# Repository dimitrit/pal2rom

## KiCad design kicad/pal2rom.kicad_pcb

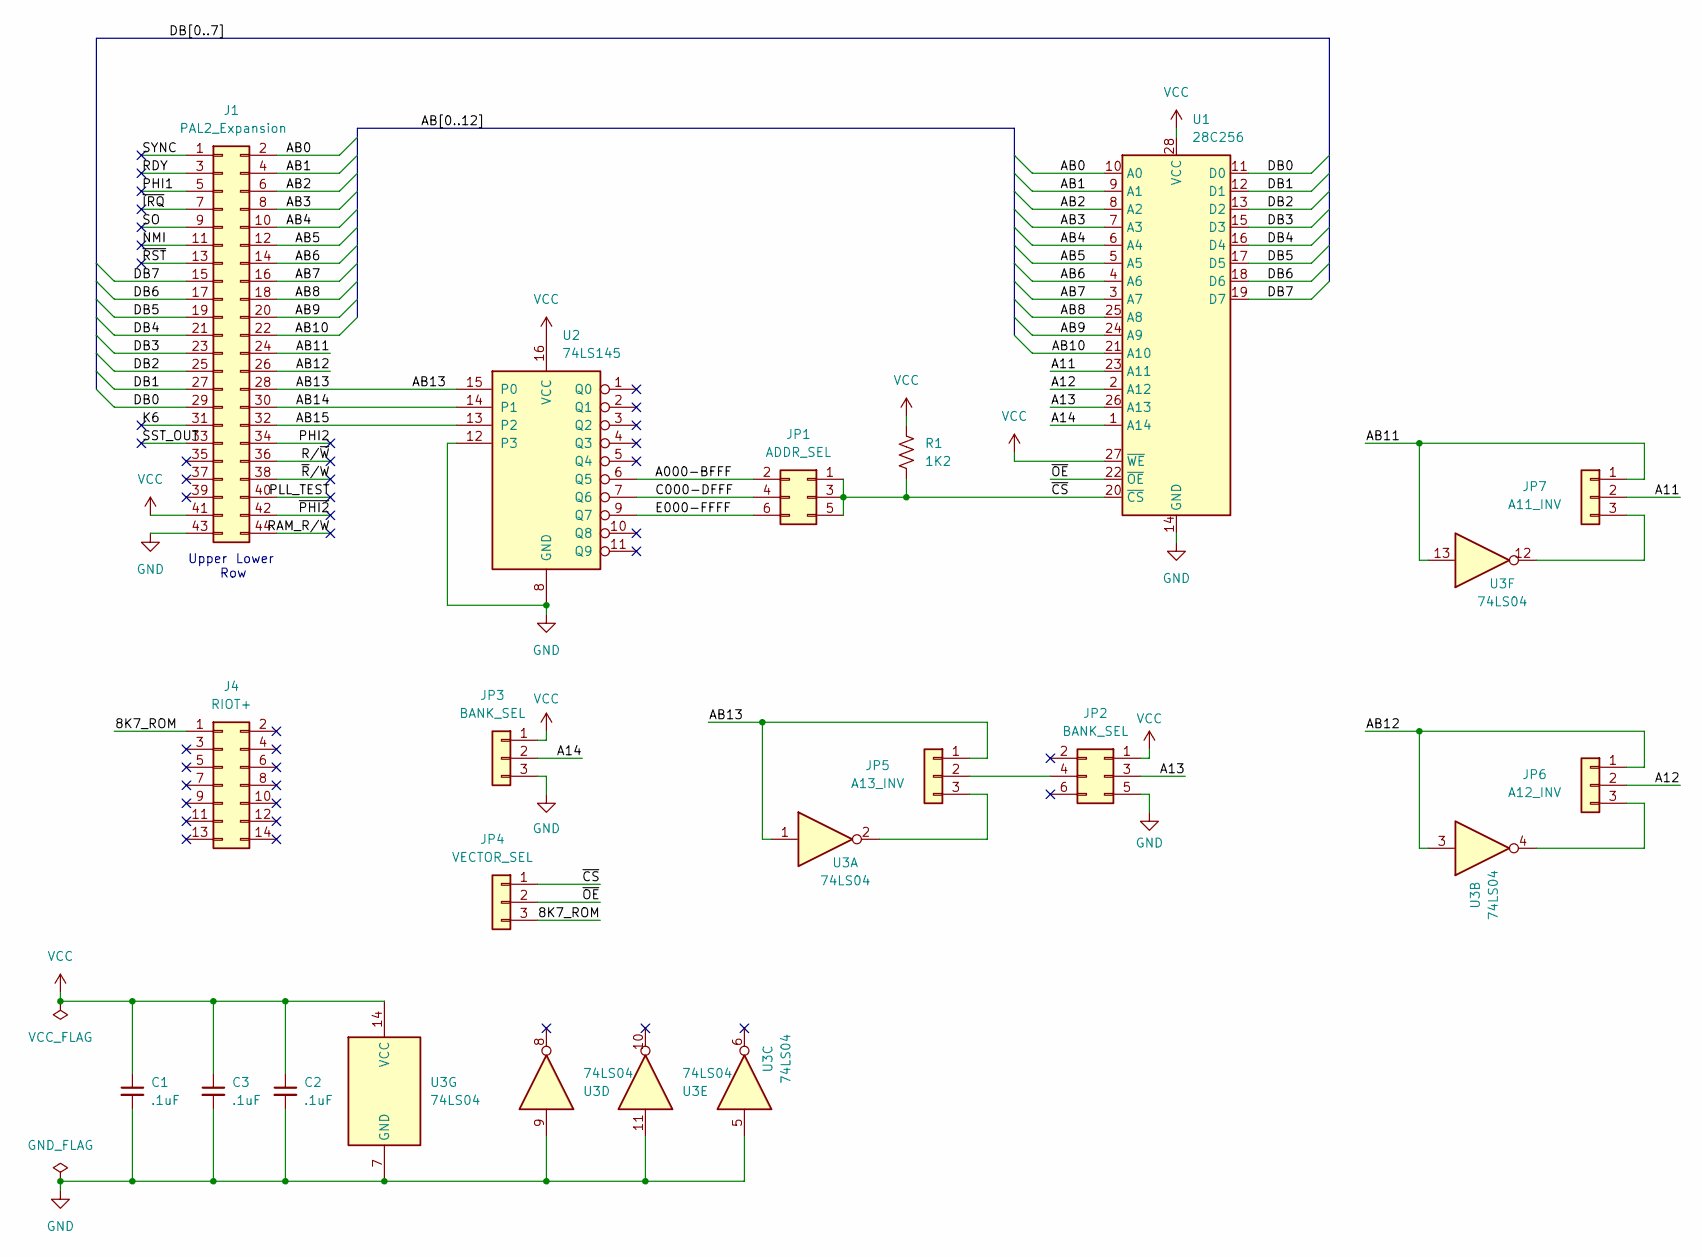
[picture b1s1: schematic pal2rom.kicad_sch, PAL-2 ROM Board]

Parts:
C1, C2, C3: .1uF; C_Disc_D5.0mm_W2.5mm_P2.50mm
J1: PAL2_Expansion; PinHeader_2x22_P2.54mm_Horizontal
J4: RIOT+; PinHeader_2x07_P2.54mm_Horizontal
JP1: ADDR_SEL; PinHeader_2x03_P2.54mm_Vertical
JP2: BANK_SEL; PinHeader_2x03_P2.54mm_Vertical
JP3: BANK_SEL; PinHeader_1x03_P2.54mm_Vertical
JP4: VECTOR_SEL; PinHeader_1x03_P2.54mm_Vertical
JP5: A13_INV; PinHeader_1x03_P2.54mm_Vertical
JP6: A12_INV; PinHeader_1x03_P2.54mm_Vertical
JP7: A11_INV; PinHeader_1x03_P2.54mm_Vertical
R1: 1K2; R_Axial_DIN0207_L6.3mm_D2.5mm_P7.62mm_Horizontal
U1: 28C256; DIP_Socket-28_W11.9mm_W12.7mm_W15.24mm_W17.78mm_W18.5mm_3M_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
U2: 74LS145; DIP-16_W7.62mm
U3: 74LS04; DIP-14_W7.62mm

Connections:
/8K7_ROM: J4.1, JP4.3
/A000-BFFF: JP1.2, U2.6 (Q5)
/A11: JP7.2, U1.23 (A11)
/A12: JP6.2, U1.2 (A12)
/A13: JP2.3, U1.26 (A13)
/A14: JP3.2, U1.1 (A14)
/AB0: J1.2, U1.10 (A0)
/AB1: J1.4, U1.9 (A1)
/AB2: J1.6, U1.8 (A2)
/AB3: J1.8, U1.7 (A3)
/AB4: J1.10, U1.6 (A4)
/AB5: J1.12, U1.5 (A5)
/AB6: J1.14, U1.4 (A6)
/AB7: J1.16, U1.3 (A7)
/AB8: J1.18, U1.25 (A8)
/AB9: J1.20, U1.24 (A9)
/AB10: J1.22, U1.21 (A10)
/AB11: J1.24, JP7.1, U3.13
/AB12: J1.26, JP6.1, U3.3
/AB13: J1.28, JP5.1, U2.15 (P0), U3.1
/AB14: J1.30, U2.14 (P1)
/AB15: J1.32, U2.13 (P2)
/C000-DFFF: JP1.4, U2.7 (Q6)
/DB0: J1.29, U1.11 (D0)
/DB1: J1.27, U1.12 (D1)
/DB2: J1.25, U1.13 (D2)
/DB3: J1.23, U1.15 (D3)
/DB4: J1.21, U1.16 (D4)
/DB5: J1.19, U1.17 (D5)
/DB6: J1.17, U1.18 (D6)
/DB7: J1.15, U1.19 (D7)
/E000-FFFF: JP1.6, U2.9 (Q7)
/K6: J1.31
/NMI: J1.11
/PHI1: J1.5
/PHI2: J1.34
/PLL_TEST: J1.40
/RAM_R/W: J1.44
/RDY: J1.3
/R/~W: J1.36
/SO: J1.9
/SST_OUT: J1.33
/SYNC: J1.1
/~CS: JP1.1, JP1.3, JP1.5, JP4.1, R1.2, U1.20 (~CS)
/~IRQ: J1.7
/~OE: JP4.2, U1.22 (~OE)
/~PHI2: J1.42
/~RST: J1.13
/~R/W: J1.38
GND: C1.2, C2.2, C3.2, J1.43, JP2.5, JP3.3, U1.14 (GND), U2.8 (GND), U2.12 (P3), U3.5, U3.7 (GND), U3.9, U3.11
unnamed: JP2.4, JP5.2
unnamed: JP5.3, U3.2
unnamed: JP6.3, U3.4
unnamed: JP7.3, U3.12
VCC: C1.1, C2.1, C3.1, J1.41, JP2.1, JP3.1, R1.1, U1.27 (~WE), U1.28 (VCC), U2.16 (VCC), U3.14 (VCC)

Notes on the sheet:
Lower
Upper
Row

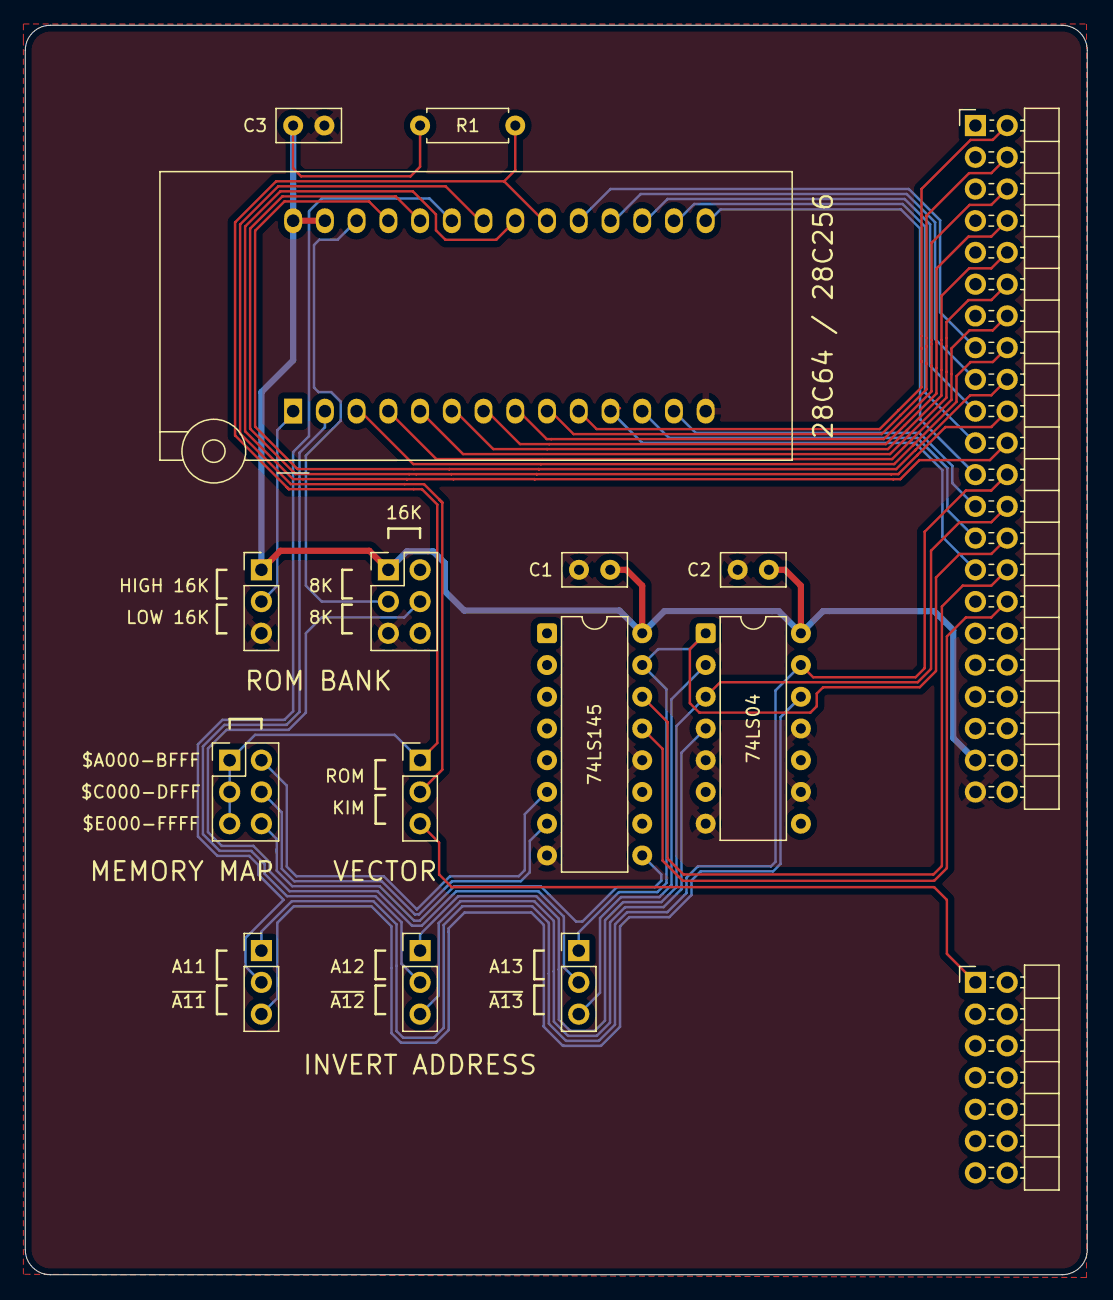
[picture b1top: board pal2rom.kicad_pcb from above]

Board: 2 copper layers, 85.0 x 100.0 mm, 16 parts (0 on the bottom side), 40 nets.
